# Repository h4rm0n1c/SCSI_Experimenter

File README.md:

# SCSI Experimenter

A 33C93A/WD33C93-based SCSI experimenter board for microcontroller projects, with a complete software architecture for running it from a Raspberry Pi Pico W or Pico 2 W.

## What it is

This repo contains:

- **KiCad hardware design** — a breakout board built around the AM33C93A/WD33C93A SCSI bus interface controller, with a 26-pin CPU header and 50-pin SCSI-1 connector, passive 220/330Ω termination, and TERMPWR direction switch (HBA/vampire modes).
- **Complete software architecture** — verified PIO firmware design for initiator and target modes, documented at `ARCHITECTURE.md` (1184 lines).
- **Verification tools** — cycle-accurate PIO timing simulation, real `pioasm` compilation checks, and KiCad netlist extraction.
- **Datasheets** — AM33C93A, WD33C93A/B, RP2040, RP2350, and SCSI-1 spec, plus extracted text layers.

## Repository structure

```
├── ARCHITECTURE.md          — Complete software architecture reference
├── scsi/                    — KiCad PCB design files
│   ├── scsi.kicad_sch       — Schematic (S-expression)
│   ├── scsi.kicad_pcb       — PCB layout
│   └── scsi.kicad_pro       — Project metadata
├── h4rm0n1c.kicad_sym       — AM33C93A/AM33C93A KiCad symbol
├── render.png               — Board render
├── docs/                    — Datasheets and references
│   ├── AM33C93A.pdf         — AMD datasheet (49 pages)
│   ├── WD33C93A.pdf         — WD variant datasheet
│   ├── WD33C93B.pdf         — Enhanced version datasheet
│   ├── WD33C93A-appnotes.pdf — Combined datasheet + app notes + errata
│   ├── SCSI-1-spec.pdf      — ANSI X3.131-1986
│   ├── RP2040-datasheet.pdf — RP2040 microcontroller
│   ├── RP2350-datasheet.pdf — RP2350 microcontroller
│   ├── PicoW-pinout-diagram.pdf
│   ├── Pico2W-pinout-diagram.pdf
│   └── PICO_GPIO_CHEATSHEET.md — Verified GPIO reference
├── docs-extracted/          — pdftotext of searchable datasheets
│   ├── WD33C93A-appnotes.txt
│   └── WD33C93B.txt
└── tools/                   — Verification tools
    ├── check_pio_timing.py  — Stage 1: timing simulator
    ├── assemble_pio.py      — Stage 2: pioasm compilation + cross-check
    ├── extract_netlist.py   — KiCad PCB netlist dumper
    └── README.md            — Tool documentation
```

## Quick start

### 1. Hardware

The board has a 26-pin CPU header (J4) that connects directly to a Pico 2 W GPIOs — no level shifters required (RP2350 GPIOs are 5V tolerant). For RP2040/Pico W builds, a 74LVC8T245 is needed on the data bus.

See `ARCHITECTURE.md` §0 (§0 for the J4 pinout and §1 for the GPIO map.

### 2. Validation

From the repo root, verify the PIO design:

```bash
python3 tools/check_pio_timing.py   # timing simulation against datasheet specs
python3 tools/assemble_pio.py       # real pioasm compilation
```

Both should exit 0.

### 3. Reading the architecture

Start with `ARCHITECTURE.md`:

- **§0–1** — Board discovery and GPIO allocation
- **§2** — PIO state machine design (register engine + burst DMA)
- **§3** — Register access layer and C API
- **§4** — SCSI bus phase engine (initiator)
- **§5** — Interrupt vs polling vs DMA analysis
- **§6** — Clock generation
- **§7** — RP2040 vs RP2350 comparison
- **Appendices F–I** — Complete register reference, interrupt codes, command reference, target mode

## Architecture highlights

- **PIO-based bus interface** — two state machines in one PIO block (22 of 32 instruction slots), driving all 33C93A register accesses with hardware-bounded strobes. No CPU bit-banging.
- **Burst DMA** — DRQ/DACK-paced PIO engine + DMA channel for data phases, zero CPU per byte, ~2.5 MB/s throughput.
- **SM clock 24 MHz** — derived from 120 MHz sysclk, chosen so all timing minima land on integer cycle counts with margin.
- **Indirect addressing** — ALE is grounded on this board, so every register access is a two-cycle operation.
- **Dual board support** — same firmware binary runs on Pico W and Pico 2 W (Pico 2 W recommended for zero-glue wiring).

## Variant support

The architecture covers the full WD33C93 family — original WD33C93, WD33C93A, WD33C93B, and AMD AM33C93A. All variant-specific features are flagged `[A+]` or `[B]` throughout the reference. The fitted chip on this board is the WD33C93B, which is used as the primary reference.

## Target mode

The 33C93A supports both initiator and target SCSI roles. The architecture covers target mode in Appendix I, including Wait-for-Select-and-Receive (0Ch) as the recommended parked state, reselection handling, and the full set of target commands. The PIO layer is identical regardless of mode.

## License

WTFPL — see the schematic title block.

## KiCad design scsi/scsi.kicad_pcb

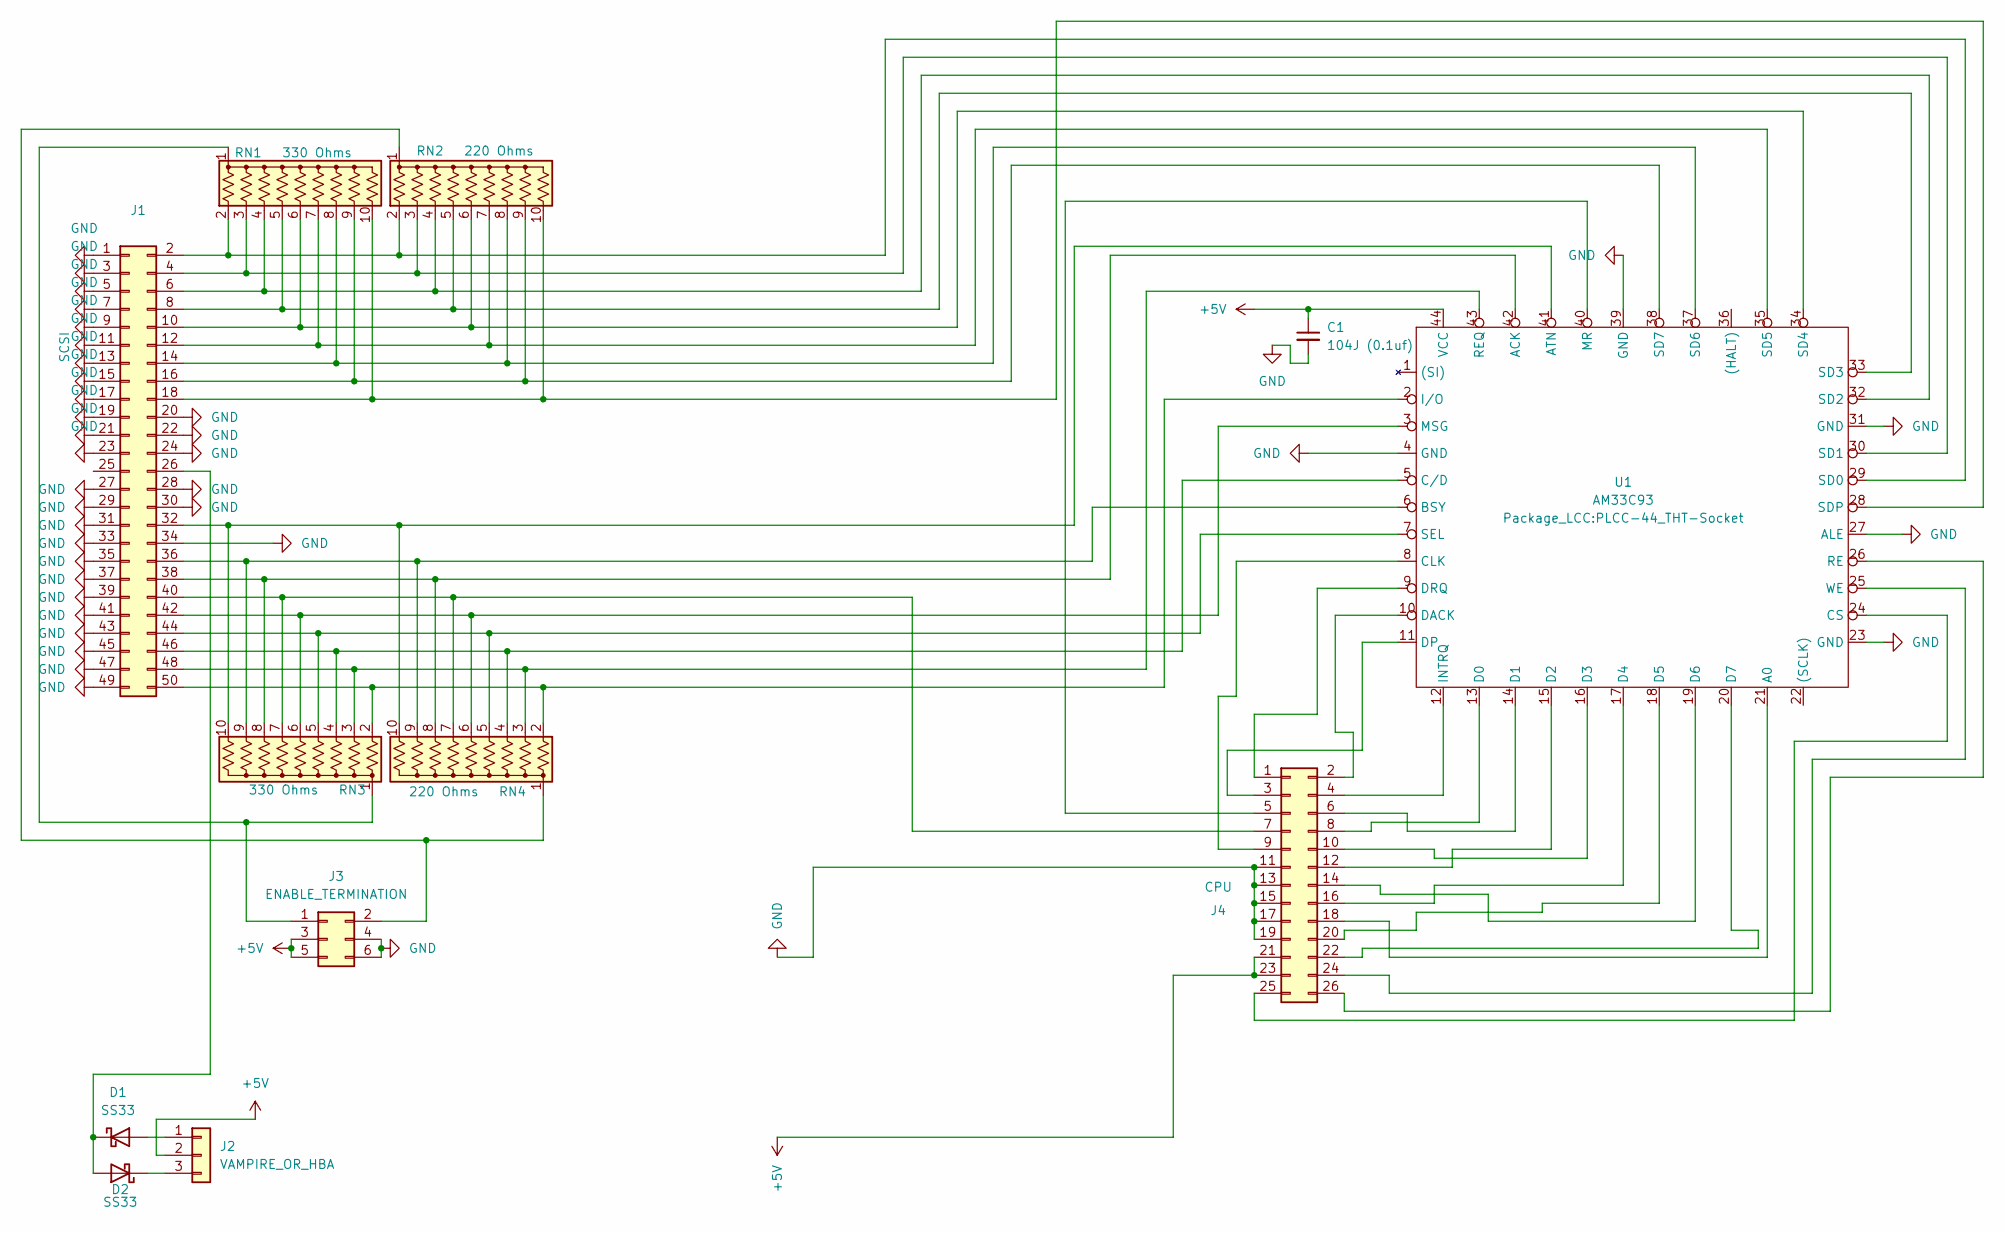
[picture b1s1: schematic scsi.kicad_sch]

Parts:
C1: 104J (0.1uf); C_Disc_D5.0mm_W2.5mm_P5.00mm
D1, D2: SS33; D_SMB-SMC_Universal_Handsoldering
J1: SCSI; IDC-Header_2x25_P2.54mm_Vertical
J2: VAMPIRE_OR_HBA; PinSocket_1x03_P2.54mm_Vertical
J3: ENABLE_TERMINATION; PinHeader_2x03_P2.54mm_Vertical
J4: CPU; PinHeader_2x13_P2.54mm_Vertical
RN1, RN3: 330 Ohms; R_Array_SIP10
RN2, RN4: 220 Ohms; R_Array_SIP10
U1: AM33C93; PLCC-44_THT-Socket

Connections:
+5V: C1.1, J2.2, J3.3, J3.5, J4.21, J4.23, U1.44 (VCC)
GND: C1.2, J1.1, J1.3, J1.5, J1.7, J1.9, J1.11, J1.13, J1.15, J1.17, J1.19, J1.20, J1.21, J1.22, J1.23, J1.24, J1.27, J1.28, J1.29, J1.30, J1.31, J1.33, J1.34, J1.35, J1.37, J1.39, J1.41, J1.43, J1.45, J1.47, J1.49, J3.4, J3.6, J4.11, J4.13, J4.15, J4.17, J4.19, U1.4 (GND), U1.23 (GND), U1.27 (ALE), U1.31 (GND), U1.39 (GND)
unnamed: D1.2 (A), J2.1
unnamed: D1.1 (K), D2.2 (A), J1.26
unnamed: D2.1 (K), J2.3
unnamed: J1.2, RN1.2 (R1), RN2.2 (R1), U1.29 (SD0)
unnamed: J1.4, RN1.3 (R2), RN2.3 (R2), U1.30 (SD1)
unnamed: J1.6, RN1.4 (R3), RN2.4 (R3), U1.32 (SD2)
unnamed: J1.8, RN1.5 (R4), RN2.5 (R4), U1.33 (SD3)
unnamed: J1.10, RN1.6 (R5), RN2.6 (R5), U1.34 (SD4)
unnamed: J1.12, RN1.7 (R6), RN2.7 (R6), U1.35 (SD5)
unnamed: J1.14, RN1.8 (R7), RN2.8 (R7), U1.37 (SD6)
unnamed: J1.16, RN1.9 (R8), RN2.9 (R8), U1.38 (SD7)
unnamed: J1.18, RN1.10 (R9), RN2.10 (R9), U1.28 (SDP)
unnamed: J1.32, RN3.10 (R9), RN4.10 (R9), U1.41 (ATN)
unnamed: J1.36, RN3.9 (R8), RN4.9 (R8), U1.6 (BSY)
unnamed: J1.38, RN3.8 (R7), RN4.8 (R7), U1.42 (ACK)
unnamed: J1.40, J4.7, RN3.7 (R6), RN4.7 (R6)
unnamed: J1.42, RN3.6 (R5), RN4.6 (R5), U1.3 (MSG)
unnamed: J1.44, RN3.5 (R4), RN4.5 (R4), U1.7 (SEL)
unnamed: J1.46, RN3.4 (R3), RN4.4 (R3), U1.5 (C/D)
unnamed: J1.48, RN3.3 (R2), RN4.3 (R2), U1.43 (REQ)
unnamed: J1.50, RN3.2 (R1), RN4.2 (R1), U1.2 (I/O)
unnamed: J3.1, RN1.1 (common), RN3.1 (common)
unnamed: J3.2, RN2.1 (common), RN4.1 (common)
unnamed: J4.1, U1.9 (DRQ)
unnamed: J4.2, U1.10 (DACK)
unnamed: J4.3, U1.11 (DP)
unnamed: J4.4, U1.12 (INTRQ)
unnamed: J4.5, U1.40 (MR)
unnamed: J4.6, U1.14 (D1)
unnamed: J4.8, U1.13 (D0)
unnamed: J4.9, U1.8 (CLK)
unnamed: J4.10, U1.16 (D3)
unnamed: J4.12, U1.15 (D2)
unnamed: J4.14, U1.19 (D6)
unnamed: J4.16, U1.17 (D4)
unnamed: J4.18, U1.21 (A0)
unnamed: J4.20, U1.18 (D5)
unnamed: J4.22, U1.20 (D7)
unnamed: J4.24, U1.25 (WE)
unnamed: J4.25, U1.24 (CS)
unnamed: J4.26, U1.26 (RE)

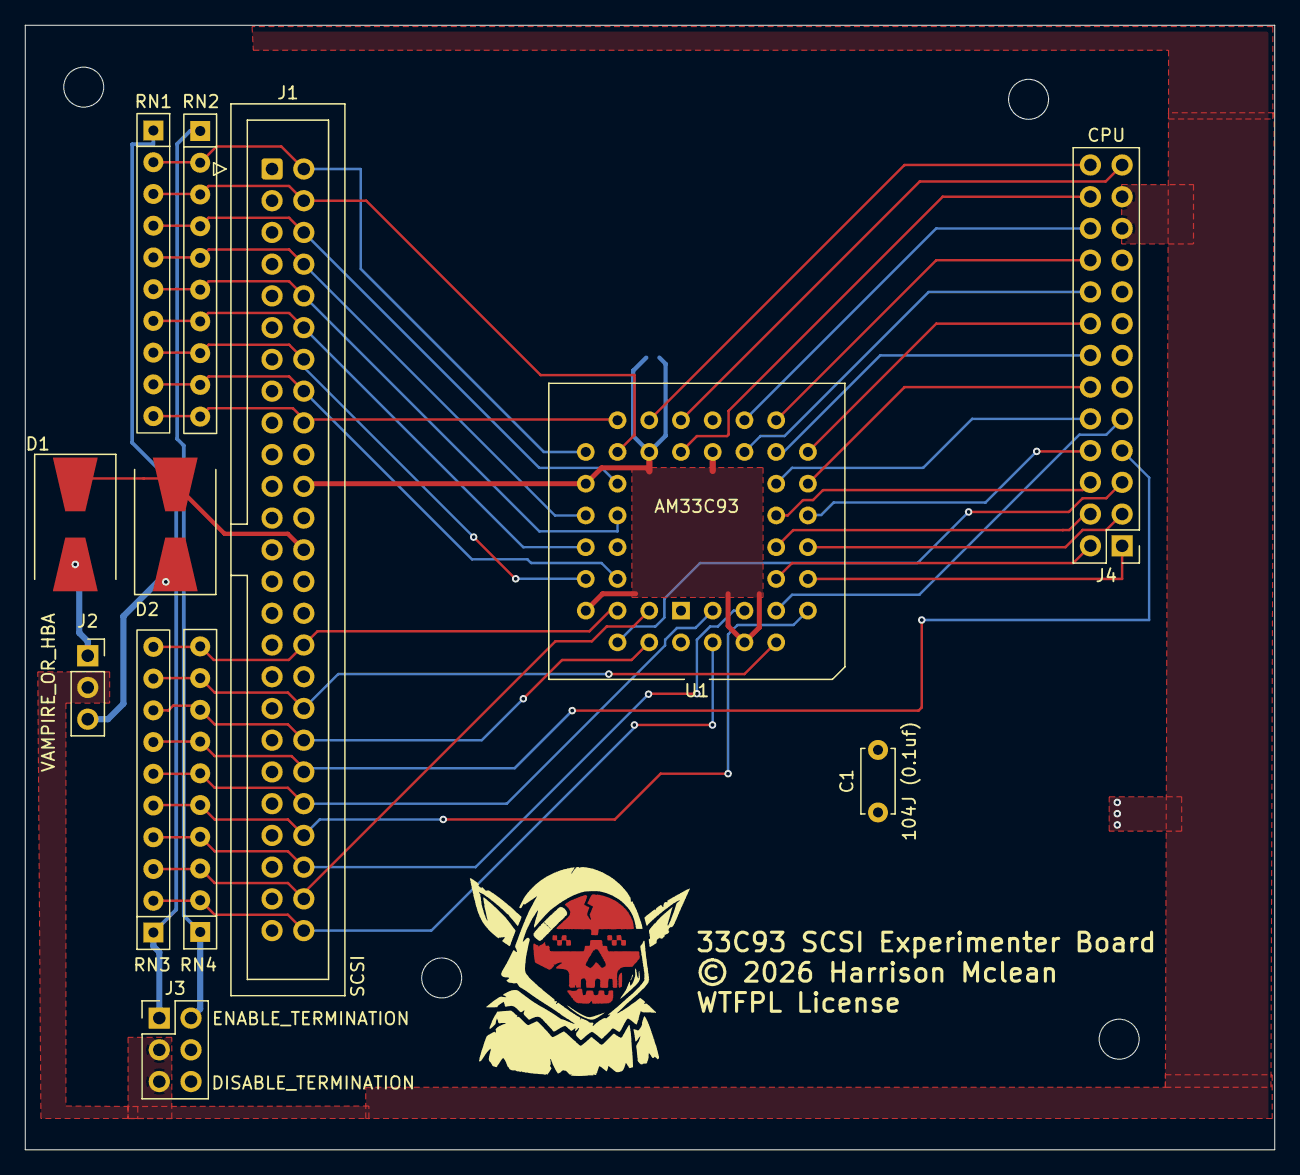
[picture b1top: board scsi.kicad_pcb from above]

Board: 2 copper layers, 100.0 x 90.0 mm, 12 parts (0 on the bottom side), 43 nets.

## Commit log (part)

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2026-02-28 Initial commit: KiCad SCSI hardware project
2026-02-28 Ignore KiCad lock files
2026-02-28 Fancied up board graphics
2026-02-28 Fixed mounting holes
2026-02-28 Fixed mounting holes - 2
2026-03-02 Final Board Design as of First Manufacture - V1.0

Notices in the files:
scsi/scsi.kicad_pcb:
© 2026 Harrison Mclean
